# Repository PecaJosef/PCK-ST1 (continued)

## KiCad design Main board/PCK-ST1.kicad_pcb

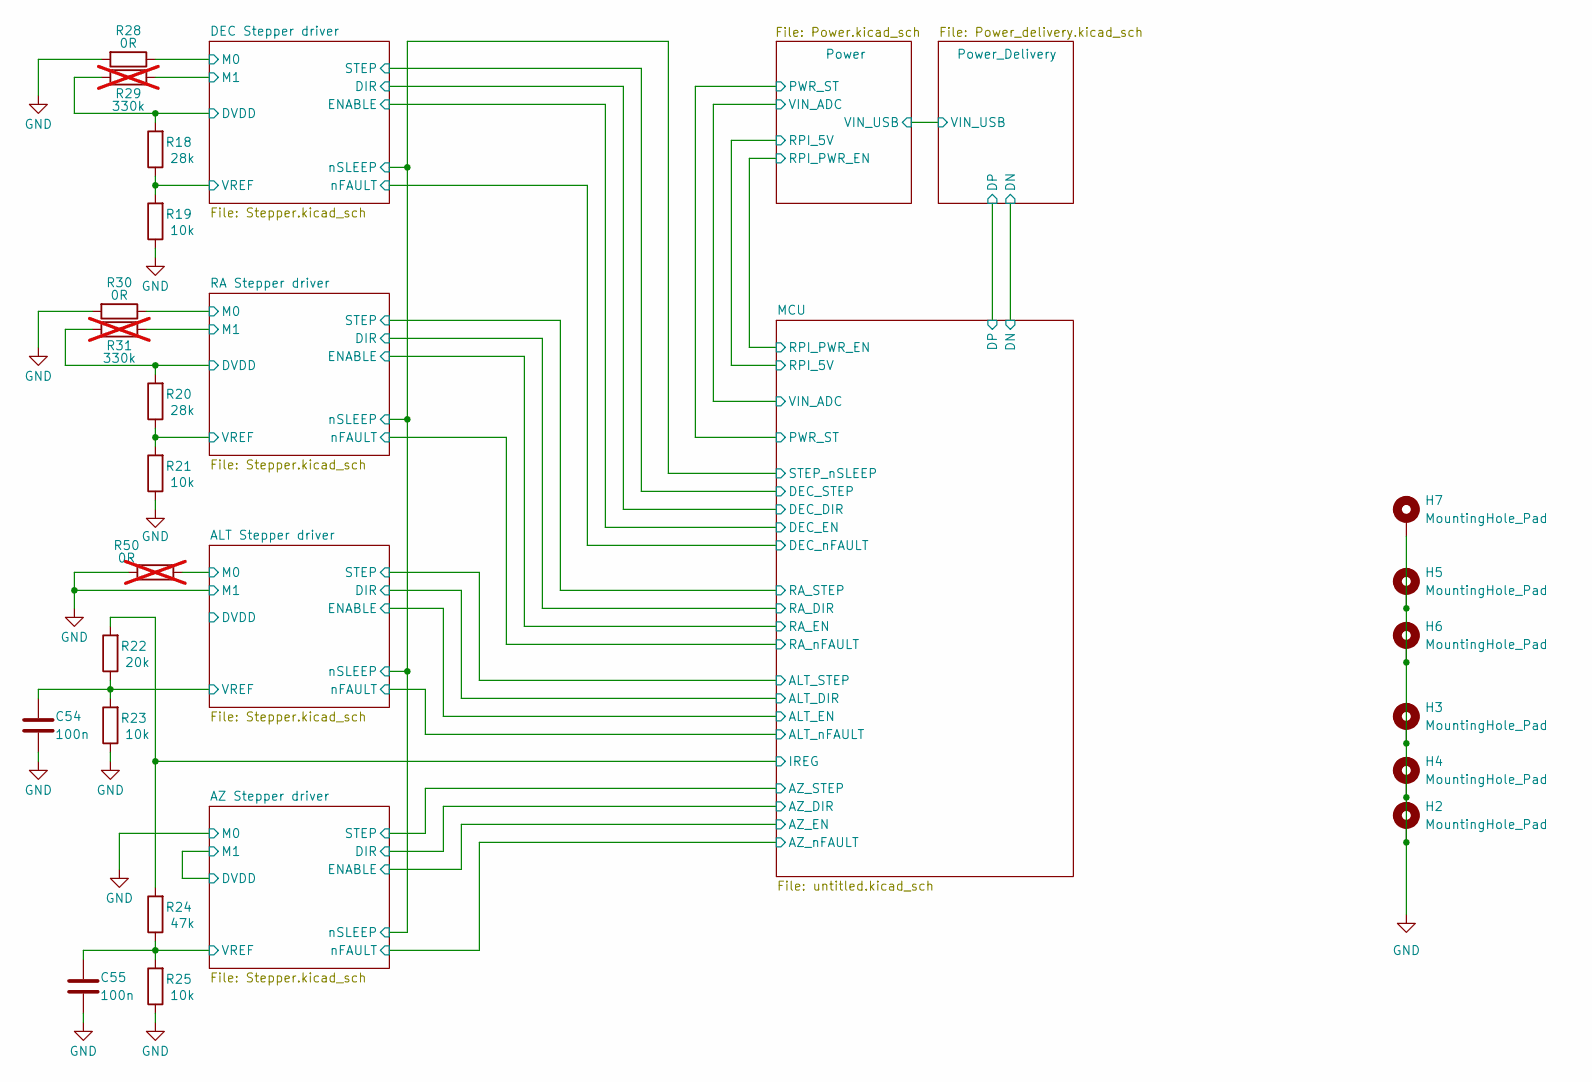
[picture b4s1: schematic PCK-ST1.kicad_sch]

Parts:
C54, C55: 100n; C_0402_1005Metric; Part Number GRM155R71C104JA88D
H2, H3, H4, H5, H6, H7: MountingHole_Pad; MountingHole_2.7mm_M2.5_DIN965_Pad
R18, R20: 28k; R_0402_1005Metric; Part Number CRCW040228K0FKED
R19, R21, R23, R25: 10k; R_0402_1005Metric; Part Number CRCW040210K0FKEDC
R22: 20k; R_0402_1005Metric; Part Number CRCW040220K0FKEDHP
R24: 47k; R_0402_1005Metric; Part Number CRCW040247K0FKED
R28, R30: 0R; R_0402_1005Metric; Part Number CRCW04020000Z0EDC
R29, R31: 330k; R_0402_1005Metric; Part Number CRCW0402330KFKED; not fitted
R50: 0R; R_0402_1005Metric; Part Number CRCW04020000Z0EDC; not fitted

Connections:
/ALT Stepper driver/M0: R50.2; also elsewhere on the board
/ALT Stepper driver/VREF: C54.1, R22.1, R23.2; also elsewhere on the board
/AZ Stepper driver/VREF: C55.1, R24.1, R25.2; also elsewhere on the board
/DEC Stepper driver/DVDD: R18.2, R29.1; also elsewhere on the board
/DEC Stepper driver/M0: R28.1; also elsewhere on the board
/DEC Stepper driver/M1: R29.2; also elsewhere on the board
/DEC Stepper driver/VREF: R18.1, R19.2; also elsewhere on the board
/MCU/IREG: R22.2, R24.2; also elsewhere on the board
/RA Stepper driver/DVDD: R20.2, R31.1; also elsewhere on the board
/RA Stepper driver/M0: R30.1; also elsewhere on the board
/RA Stepper driver/M1: R31.2; also elsewhere on the board
/RA Stepper driver/VREF: R20.1, R21.2; also elsewhere on the board
GND: C54.2, C55.2, H2.1, H3.1, H4.1, H5.1, H6.1, H7.1, R19.1, R21.1, R23.1, R25.1, R28.2, R30.2, R50.1; also elsewhere on the board

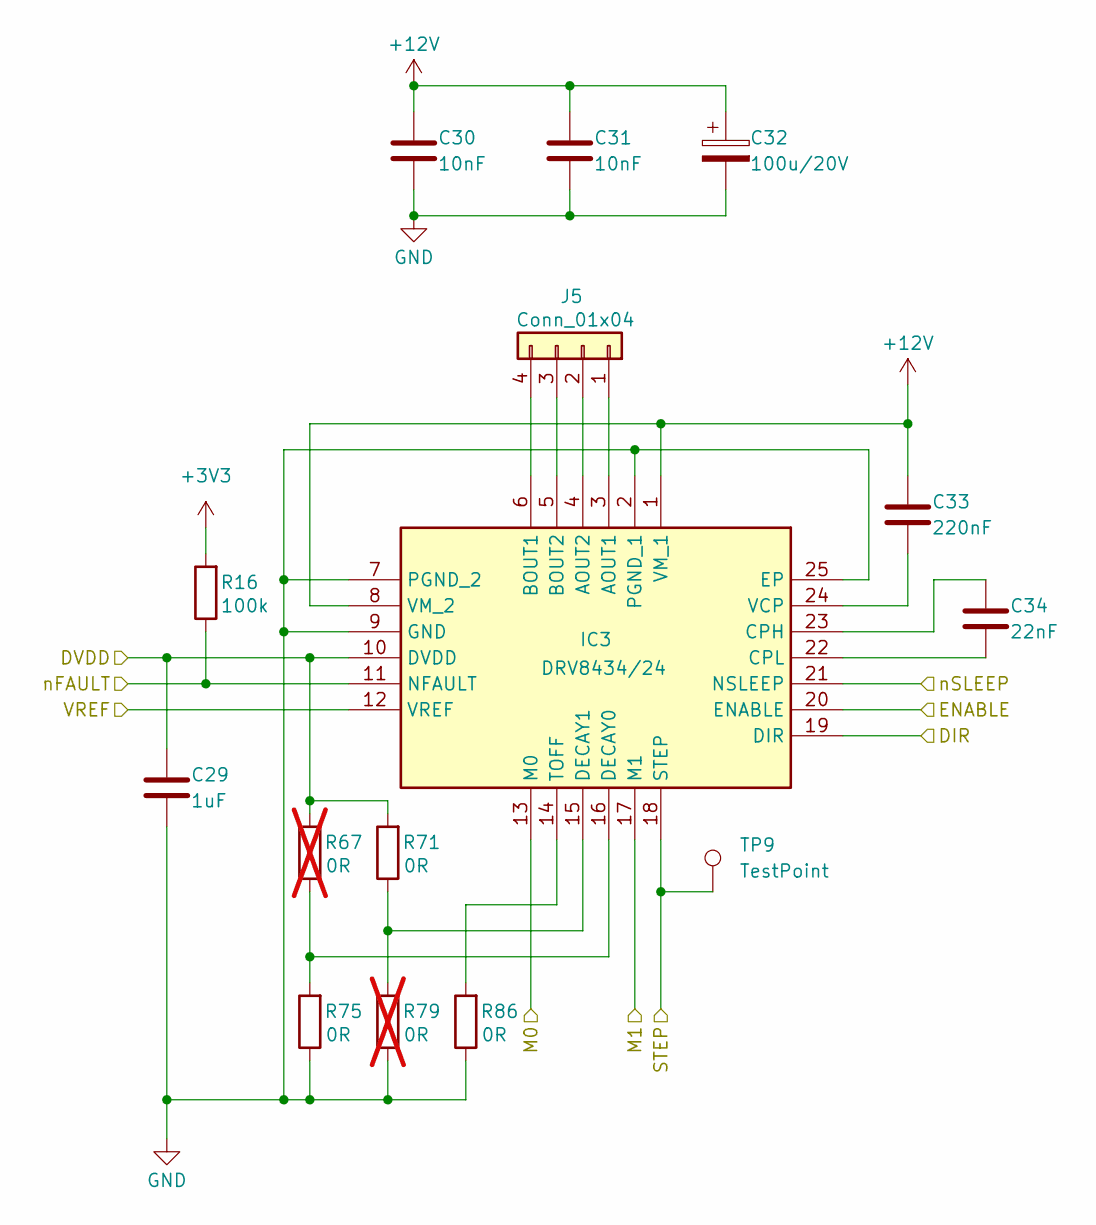
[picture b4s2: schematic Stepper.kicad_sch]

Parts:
C29: 1uF; C_0402_1005Metric; Part Number GRM155Z71A105KE01J
C30, C31: 10nF; C_0402_1005Metric; Part Number GRM155R71H103JA88D
C32: 100u/20V; CP_EIA-7343-15_Kemet-W; Part Number 293D107X9020D2TE3
C33: 220nF; C_0402_1005Metric; Part Number GCM155R71C224KE02J
C34: 22nF; C_0402_1005Metric; Part Number GRM155R71E223JA61D
IC3: DRV8434/24; QFN50P400X400X100-25N-D; Mouser Part Number DRV8434RGER
J5: Conn_01x04; JST_PH_B4B-PH-K_1x04_P2.00mm_Vertical
R16: 100k; R_0402_1005Metric; Part Number CRCW0402100KFKEE
R67, R79: 0R; R_0402_1005Metric; Part Number CRCW04020000Z0EDC; not fitted
R71, R75, R86: 0R; R_0402_1005Metric; Part Number CRCW04020000Z0EDC
TP9: TestPoint; TestPoint_Pad_D1.0mm

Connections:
+3V3: R16.2; also elsewhere on the board
+12V: C30.1, C31.1, C32.1, C33.1, IC3.1 (VM_1), IC3.8 (VM_2); also elsewhere on the board
/ALT Stepper driver/DIR: IC3.19 (DIR); also elsewhere on the board
/ALT Stepper driver/DVDD: C29.1, IC3.10 (DVDD), R67.2, R71.2
/ALT Stepper driver/ENABLE: IC3.20 (ENABLE); also elsewhere on the board
/ALT Stepper driver/M0: IC3.13 (M0); also elsewhere on the board
/ALT Stepper driver/STEP: IC3.18 (STEP), TP9.1; also elsewhere on the board
/ALT Stepper driver/VREF: IC3.12 (VREF); also elsewhere on the board
/ALT Stepper driver/nFAULT: IC3.11 (NFAULT), R16.1; also elsewhere on the board
/ALT Stepper driver/nSLEEP: IC3.21 (NSLEEP); also elsewhere on the board
GND: C29.2, C30.2, C31.2, C32.2, IC3.2 (PGND_1), IC3.7 (PGND_2), IC3.9 (GND), IC3.17 (M1), IC3.25 (EP), R75.1, R79.1, R86.1; also elsewhere on the board
unnamed: IC3.3 (AOUT1), J5.1
unnamed: IC3.4 (AOUT2), J5.2
unnamed: IC3.6 (BOUT1), J5.4
unnamed: IC3.5 (BOUT2), J5.3
unnamed: C34.1, IC3.23 (CPH)
unnamed: C34.2, IC3.22 (CPL)
unnamed: IC3.16 (DECAY0), R67.1, R75.2
unnamed: IC3.15 (DECAY1), R71.1, R79.2
unnamed: IC3.14 (TOFF), R86.2
unnamed: C33.2, IC3.24 (VCP)

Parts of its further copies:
C15, C28, C40: 22nF; C_0402_1005Metric; Part Number GRM155R71E223JA61D
C16, C23, C35: 1uF; C_0402_1005Metric; Part Number GRM155Z71A105KE01J
C17, C27, C39: 220nF; C_0402_1005Metric; Part Number GCM155R71C224KE02J
C18, C19, C24, C25, C36, C37: 10nF; C_0402_1005Metric; Part Number GRM155R71H103JA88D
C20, C26, C38: 100u/20V; CP_EIA-7343-15_Kemet-W; Part Number 293D107X9020D2TE3
IC1, IC2, IC4: DRV8434/24; QFN50P400X400X100-25N-D; Mouser Part Number DRV8434RGER
J3, J4, J6: Conn_01x04; JST_PH_B4B-PH-K_1x04_P2.00mm_Vertical
R14, R15, R17: 100k; R_0402_1005Metric; Part Number CRCW0402100KFKEE
R65, R66, R68, R77, R78, R80: 0R; R_0402_1005Metric; Part Number CRCW04020000Z0EDC; not fitted
R69, R70, R72, R73, R74, R76, R82, R84, R88: 0R; R_0402_1005Metric; Part Number CRCW04020000Z0EDC
TP7, TP8, TP10: TestPoint; TestPoint_Pad_D1.0mm

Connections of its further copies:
+3V3: R14.2, R15.2, R17.2; also elsewhere on the board
+12V: C17.1, C18.1, C19.1, C20.1, C24.1, C25.1, C26.1, C27.1, C36.1, C37.1, C38.1, C39.1, IC1.1 (VM_1), IC1.8 (VM_2), IC2.1 (VM_1), IC2.8 (VM_2), IC4.1 (VM_1), IC4.8 (VM_2); also elsewhere on the board
/ALT Stepper driver/nSLEEP: IC1.21 (NSLEEP), IC2.21 (NSLEEP), IC4.21 (NSLEEP); also elsewhere on the board
/AZ Stepper driver/DIR: IC4.19 (DIR); also elsewhere on the board
/AZ Stepper driver/DVDD: C35.1, IC4.10 (DVDD), IC4.17 (M1), R68.2, R72.2
/AZ Stepper driver/ENABLE: IC4.20 (ENABLE); also elsewhere on the board
/AZ Stepper driver/STEP: IC4.18 (STEP), TP10.1; also elsewhere on the board
/AZ Stepper driver/VREF: IC4.12 (VREF); also elsewhere on the board
/AZ Stepper driver/nFAULT: IC4.11 (NFAULT), R17.1; also elsewhere on the board
/DEC Stepper driver/DIR: IC1.19 (DIR); also elsewhere on the board
/DEC Stepper driver/DVDD: C16.1, IC1.10 (DVDD), R65.2, R69.2; also elsewhere on the board
/DEC Stepper driver/ENABLE: IC1.20 (ENABLE); also elsewhere on the board
/DEC Stepper driver/M0: IC1.13 (M0); also elsewhere on the board
/DEC Stepper driver/M1: IC1.17 (M1); also elsewhere on the board
/DEC Stepper driver/STEP: IC1.18 (STEP), TP7.1; also elsewhere on the board
/DEC Stepper driver/VREF: IC1.12 (VREF); also elsewhere on the board
/DEC Stepper driver/nFAULT: IC1.11 (NFAULT), R14.1; also elsewhere on the board
/MCU/RA_DIR: IC2.19 (DIR); also elsewhere on the board
/MCU/RA_EN: IC2.20 (ENABLE); also elsewhere on the board
/MCU/RA_STEP: IC2.18 (STEP), TP8.1; also elsewhere on the board
/MCU/RA_nFAULT: IC2.11 (NFAULT), R15.1; also elsewhere on the board
/RA Stepper driver/DVDD: C23.1, IC2.10 (DVDD), R66.2, R70.2; also elsewhere on the board
/RA Stepper driver/M0: IC2.13 (M0); also elsewhere on the board
/RA Stepper driver/M1: IC2.17 (M1); also elsewhere on the board
/RA Stepper driver/VREF: IC2.12 (VREF); also elsewhere on the board
GND: C16.2, C18.2, C19.2, C20.2, C23.2, C24.2, C25.2, C26.2, C35.2, C36.2, C37.2, C38.2, IC1.2 (PGND_1), IC1.7 (PGND_2), IC1.9 (GND), IC1.25 (EP), IC2.2 (PGND_1), IC2.7 (PGND_2), IC2.9 (GND), IC2.25 (EP), IC4.2 (PGND_1), IC4.7 (PGND_2), IC4.9 (GND), IC4.13 (M0), IC4.25 (EP), R73.1, R74.1, R76.1, R77.1, R78.1, R80.1, R82.1, R84.1, R88.1; also elsewhere on the board
unnamed: IC1.3 (AOUT1), J3.1
unnamed: IC1.4 (AOUT2), J3.2
unnamed: IC1.6 (BOUT1), J3.4
unnamed: IC1.5 (BOUT2), J3.3
unnamed: C15.1, IC1.23 (CPH)
unnamed: C15.2, IC1.22 (CPL)
unnamed: IC1.16 (DECAY0), R65.1, R73.2
unnamed: IC1.15 (DECAY1), R69.1, R77.2
unnamed: IC1.14 (TOFF), R82.2
unnamed: C17.2, IC1.24 (VCP)
unnamed: IC2.3 (AOUT1), J4.1
unnamed: IC2.4 (AOUT2), J4.2
unnamed: IC2.6 (BOUT1), J4.4
unnamed: IC2.5 (BOUT2), J4.3
unnamed: C28.1, IC2.23 (CPH)
unnamed: C28.2, IC2.22 (CPL)
unnamed: IC2.16 (DECAY0), R66.1, R74.2
unnamed: IC2.15 (DECAY1), R70.1, R78.2
unnamed: IC2.14 (TOFF), R84.2
unnamed: C27.2, IC2.24 (VCP)
unnamed: IC4.3 (AOUT1), J6.1
unnamed: IC4.4 (AOUT2), J6.2
unnamed: IC4.6 (BOUT1), J6.4
unnamed: IC4.5 (BOUT2), J6.3
unnamed: C40.1, IC4.23 (CPH)
unnamed: C40.2, IC4.22 (CPL)
unnamed: IC4.16 (DECAY0), R68.1, R76.2
unnamed: IC4.15 (DECAY1), R72.1, R80.2
unnamed: IC4.14 (TOFF), R88.2
unnamed: C39.2, IC4.24 (VCP)

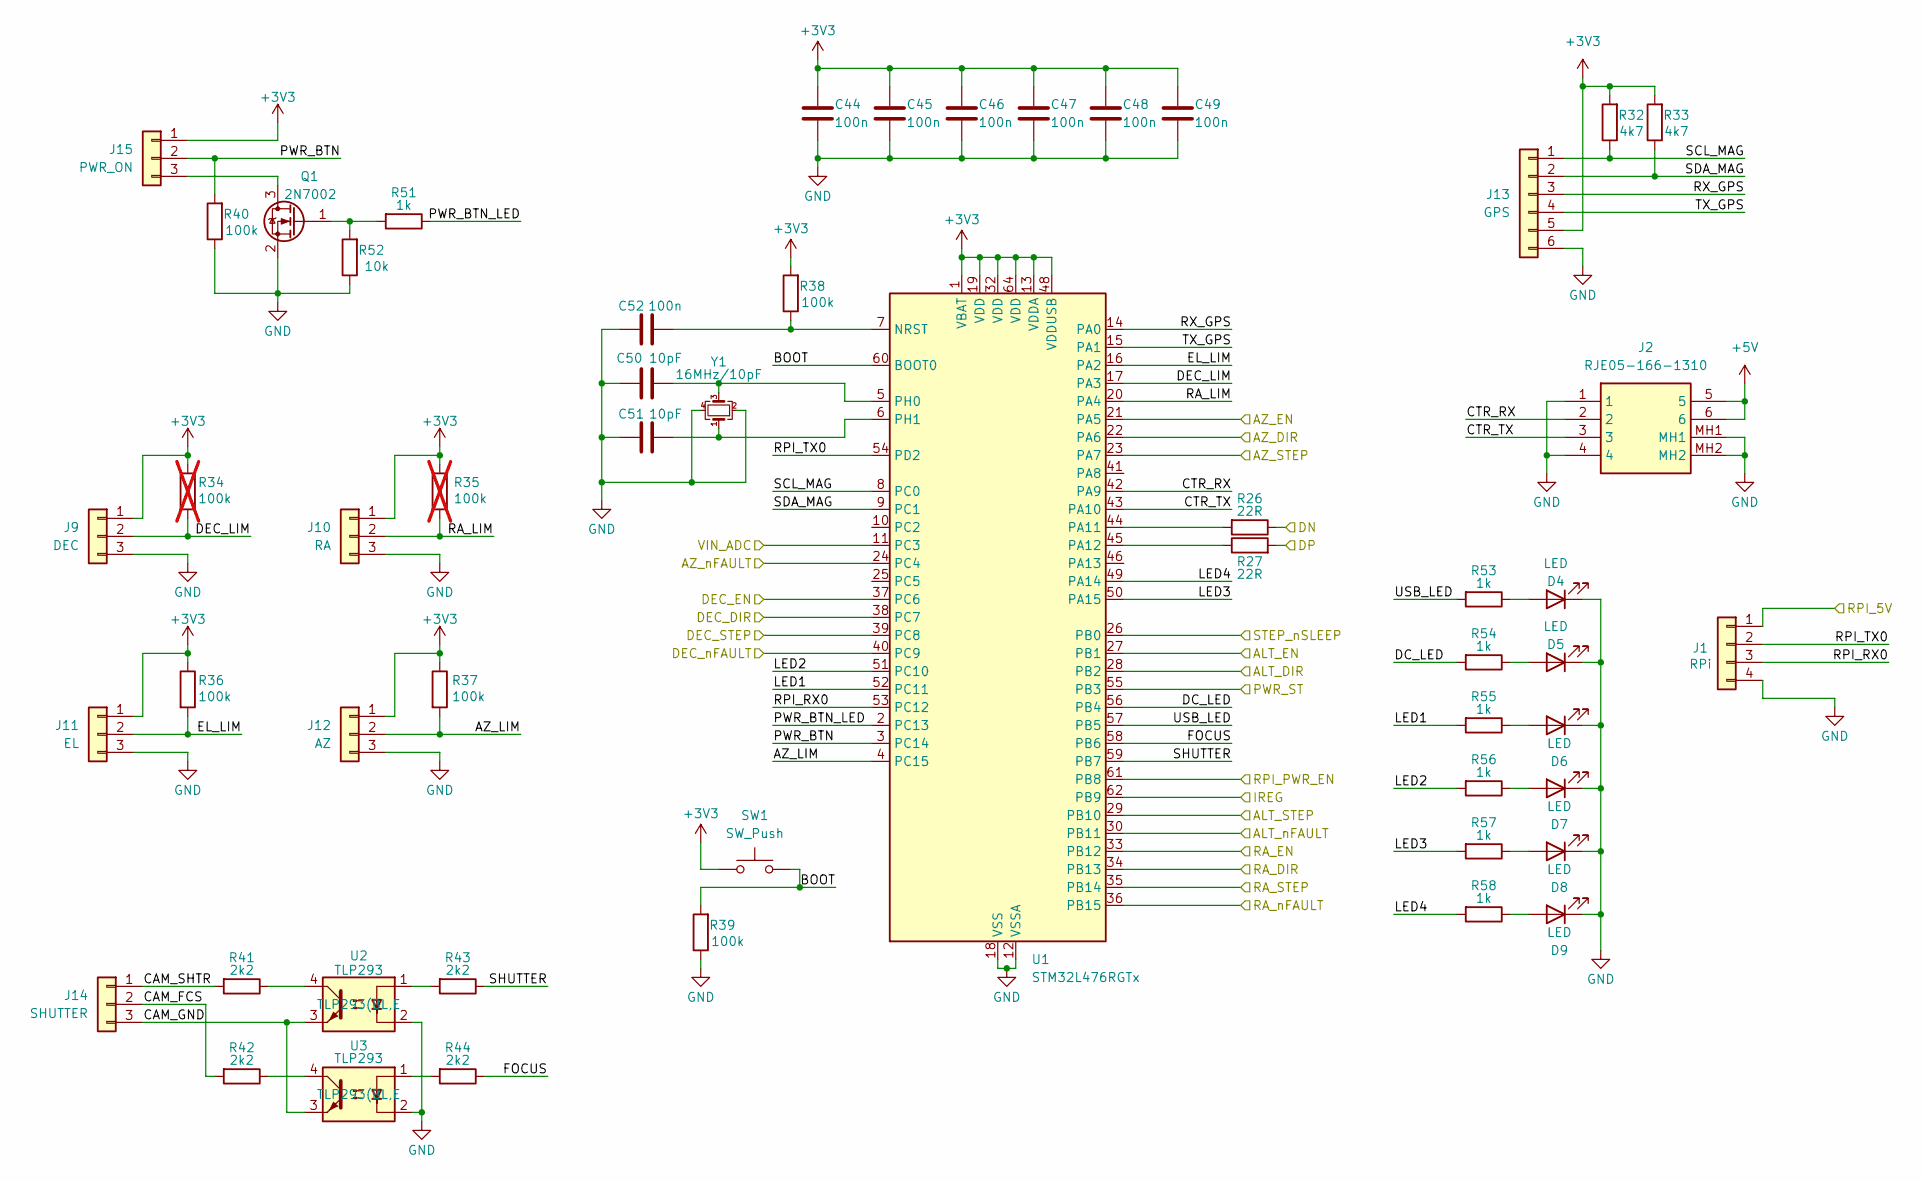
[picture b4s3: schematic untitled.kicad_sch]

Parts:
C44, C45, C46, C47, C48, C49, C52: 100n; C_0402_1005Metric; Part Number GRM155R71C104JA88D
C50, C51: 10pF; C_0402_1005Metric; Part Number GCM1555C1H100FA16D
D4, D5, D6, D7, D8, D9: LED; LED_0603_1608Metric; Part Number SML-D12U1WT86
J1: RPi; JST_PH_B4B-PH-K_1x04_P2.00mm_Vertical
J2: RJE05-166-1310; RJE051661310; Mouser Part Number 523-RJE05-166-1310
J9: DEC; JST_PH_B3B-PH-K_1x03_P2.00mm_Vertical
J10: RA; JST_PH_B3B-PH-K_1x03_P2.00mm_Vertical
J11: EL; JST_PH_B3B-PH-K_1x03_P2.00mm_Vertical
J12: AZ; JST_PH_B3B-PH-K_1x03_P2.00mm_Vertical
J13: GPS; JST_PH_B6B-PH-K_1x06_P2.00mm_Vertical
J14: SHUTTER; JST_PH_B3B-PH-K_1x03_P2.00mm_Vertical
J15: PWR_ON; JST_PH_B3B-PH-K_1x03_P2.00mm_Vertical
Q1: 2N7002; SOT-323_SC-70; Part Number 2N7002AKW-QX
R26, R27: 22R; R_0402_1005Metric; Part Number CRCW040222R0FKED
R32, R33: 4k7; R_0402_1005Metric; Part Number CRCW04024K70FKED
R34, R35: 100k; R_0402_1005Metric; Part Number CRCW0402100KFKEE; not fitted
R36, R37, R38, R39, R40: 100k; R_0402_1005Metric; Part Number CRCW0402100KFKEE
R41, R42, R43, R44: 2k2; R_0402_1005Metric; Part Number CRCW04022K20FKEDC
R51, R53, R54, R55, R56, R57, R58: 1k; R_0402_1005Metric; Part Number CRCW04021K00FKED
R52: 10k; R_0402_1005Metric; Part Number CRCW040210K0FKEDC
SW1: SW_Push; SKRTLAE010
U1: STM32L476RGTx; LQFP-64_10x10mm_P0.5mm; Part Number STM32L476RGT6
U2, U3: TLP293; SOIC-4_4.55x2.6mm_P1.27mm; Part Number TLP293(BL,E
Y1: 16MHz/10pF; Crystal_SMD_2016-4Pin_2.0x1.6mm; Part Number ECS1601037B2CTNTR

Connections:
+3V3: C44.1, C45.1, C46.1, C47.1, C48.1, C49.1, J9.1, J10.1, J11.1, J12.1, J13.5, J15.1, R32.2, R33.2, R34.1, R35.1, R36.1, R37.1, R38.2, SW1.1, U1.1 (VBAT), U1.13 (VDDA), U1.19 (VDD), U1.32 (VDD), U1.48 (VDDUSB), U1.64 (VDD); also elsewhere on the board
+5V: J2.5, J2.6; also elsewhere on the board
/ALT Stepper driver/DIR: U1.28 (PB2); also elsewhere on the board
/ALT Stepper driver/ENABLE: U1.27 (PB1); also elsewhere on the board
/ALT Stepper driver/STEP: U1.29 (PB10); also elsewhere on the board
/ALT Stepper driver/nFAULT: U1.30 (PB11); also elsewhere on the board
/ALT Stepper driver/nSLEEP: U1.26 (PB0); also elsewhere on the board
/AZ Stepper driver/DIR: U1.22 (PA6); also elsewhere on the board
/AZ Stepper driver/ENABLE: U1.21 (PA5); also elsewhere on the board
/AZ Stepper driver/STEP: U1.23 (PA7); also elsewhere on the board
/AZ Stepper driver/nFAULT: U1.24 (PC4); also elsewhere on the board
/DEC Stepper driver/DIR: U1.38 (PC7); also elsewhere on the board
/DEC Stepper driver/ENABLE: U1.37 (PC6); also elsewhere on the board
/DEC Stepper driver/STEP: U1.39 (PC8); also elsewhere on the board
/DEC Stepper driver/nFAULT: U1.40 (PC9); also elsewhere on the board
/MCU/AZ_LIM: J12.2, R37.2, U1.4 (PC15)
/MCU/BOOT: R39.2, SW1.2, U1.60 (BOOT0)
/MCU/CAM_FCS: J14.2, R42.2
/MCU/CAM_GND: J14.3, U2.3, U3.3
/MCU/CAM_SHTR: J14.1, R41.2
/MCU/CTR_RX: J2.2, U1.42 (PA9)
/MCU/CTR_TX: J2.3, U1.43 (PA10)
/MCU/DC_LED: R54.2, U1.56 (PB4)
/MCU/DEC_LIM: J9.2, R34.2, U1.17 (PA3)
/MCU/DN: R26.1; also elsewhere on the board
/MCU/DP: R27.2; also elsewhere on the board
/MCU/EL_LIM: J11.2, R36.2, U1.16 (PA2)
/MCU/FOCUS: R44.1, U1.58 (PB6)
/MCU/IREG: U1.62 (PB9); also elsewhere on the board
/MCU/LED1: R55.2, U1.52 (PC11)
/MCU/LED2: R56.2, U1.51 (PC10)
/MCU/LED3: R57.2, U1.50 (PA15)
/MCU/LED4: R58.2, U1.49 (PA14)
/MCU/PWR_BTN: J15.2, R40.2, U1.3 (PC14)
/MCU/PWR_BTN_LED: R51.1, U1.2 (PC13)
/MCU/RA_DIR: U1.34 (PB13); also elsewhere on the board
/MCU/RA_EN: U1.33 (PB12); also elsewhere on the board
/MCU/RA_LIM: J10.2, R35.2, U1.20 (PA4)
/MCU/RA_STEP: U1.35 (PB14); also elsewhere on the board
/MCU/RA_nFAULT: U1.36 (PB15); also elsewhere on the board
/MCU/RPI_5V: J1.1; also elsewhere on the board
/MCU/RPI_PWR_EN: U1.61 (PB8); also elsewhere on the board
/MCU/RPI_RX0: J1.3, U1.53 (PC12)
/MCU/RPI_TX0: J1.2, U1.54 (PD2)
/MCU/RX_GPS: J13.3, U1.14 (PA0)
/MCU/SCL_MAG: J13.1, R32.1, U1.8 (PC0)
/MCU/SDA_MAG: J13.2, R33.1, U1.9 (PC1)
/MCU/SHUTTER: R43.1, U1.59 (PB7)
/MCU/TX_GPS: J13.4, U1.15 (PA1)
/MCU/USB_LED: R53.2, U1.57 (PB5)
/MCU/VIN_ADC: U1.11 (PC3); also elsewhere on the board
/Power/PWR_STATE: U1.55 (PB3); also elsewhere on the board
GND: C44.2, C45.2, C46.2, C47.2, C48.2, C49.2, C50.1, C51.1, C52.1, D4.1 (K), D5.1 (K), D6.1 (K), D7.1 (K), D8.1 (K), D9.1 (K), J1.4, J2.1, J2.4, J2.MH1, J2.MH2, J9.3, J10.3, J11.3, J12.3, J13.6, Q1.2 (S), R39.1, R40.1, R52.1, U1.12 (VSSA), U1.18 (VSS), U1.31 (VSS), U1.47 (VSS), U1.63 (VSS), U2.2, U3.2, Y1.2, Y1.4; also elsewhere on the board
unnamed: D4.2 (A), R53.1
unnamed: D5.2 (A), R54.1
unnamed: D6.2 (A), R55.1
unnamed: D7.2 (A), R56.1
unnamed: D8.2 (A), R57.1
unnamed: D9.2 (A), R58.1
unnamed: J15.3, Q1.3 (D)
unnamed: Q1.1 (G), R51.2, R52.2
unnamed: R41.1, U2.4
unnamed: R42.1, U3.4
unnamed: R43.2, U2.1
unnamed: R44.2, U3.1
unnamed: C52.2, R38.1, U1.7 (NRST)
unnamed: R26.2, U1.44 (PA11)
unnamed: R27.1, U1.45 (PA12)
unnamed: C50.2, U1.5 (PH0), Y1.3
unnamed: C51.2, U1.6 (PH1), Y1.1

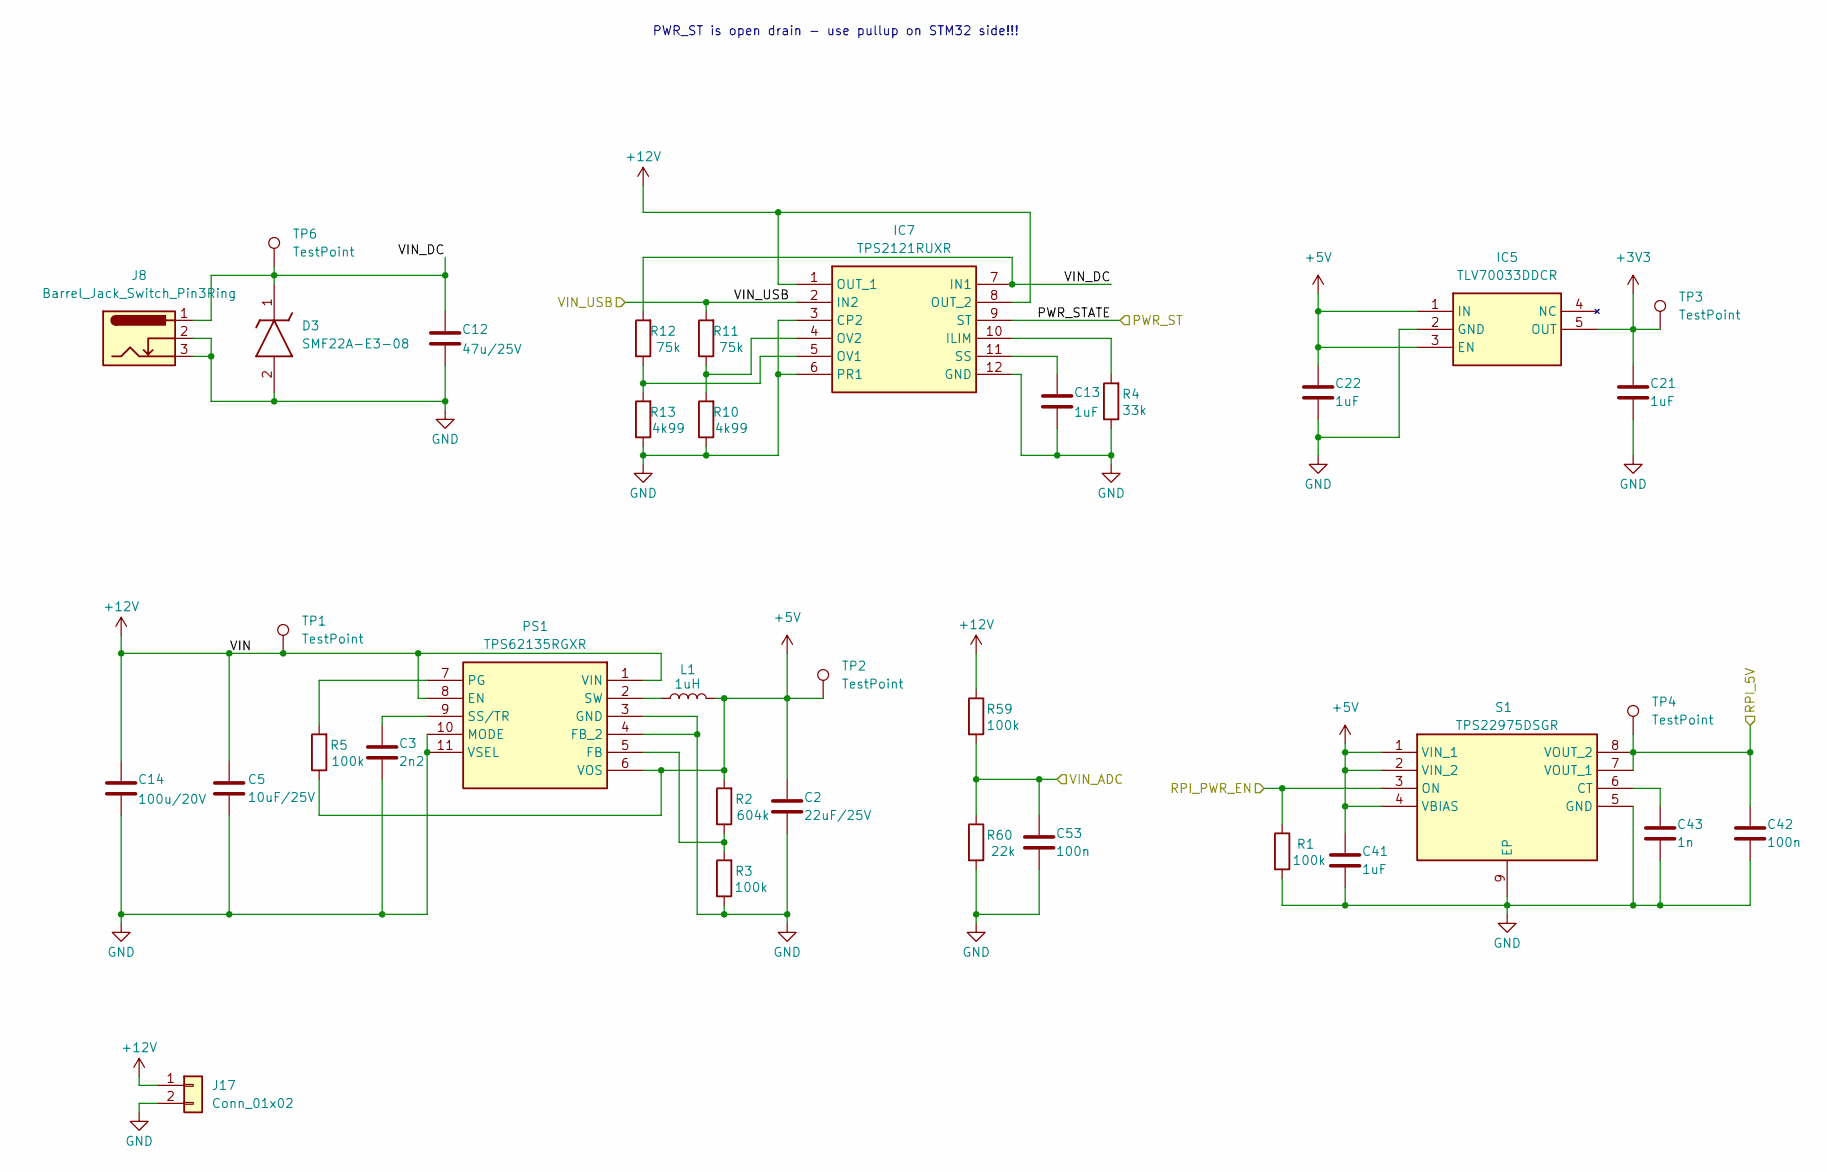
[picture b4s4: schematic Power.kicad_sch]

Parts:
C2: 22uF/25V; C_0805_2012Metric; Part Number CL21A226MAYNNNE
C3: 2n2; C_0402_1005Metric; Part Number GRM155R71H222JA01J
C5: 10uF/25V; C_0603_1608Metric; Part Number GRM188R61E106KA73J
C12: 47u/25V; C_1206_3216Metric; Part Number C3216X5R1E476M160AC
C13, C21, C22, C41: 1uF; C_0402_1005Metric; Part Number GRM155Z71A105KE01J
C14: 100u/20V; CP_EIA-7343-15_Kemet-W; Part Number 293D107X9020D2TE3
C42, C53: 100n; C_0402_1005Metric; Part Number GRM155R71C104JA88D
C43: 1n; C_0402_1005Metric; Part Number GRT1555C1H102FA02D
D3: SMF22A-E3-08; SODFL3718X108N; Mouser Part Number 78-SMF22A-E3-08
IC5: TLV70033DDCR; SOT95P280X110-5N; Mouser Part Number 595-TLV70033DDCR
IC7: TPS2121RUXR; Mouser Part Number 595-TPS2121RUXR
J8: Barrel_Jack_Switch_Pin3Ring; BarrelJack_GCT_DCJ200-10-A_Horizontal
J17: Conn_01x02; JST_PH_B2B-PH-K_1x02_P2.00mm_Vertical
L1: 1uH; L_Coilcraft_XAL4020-XXX; Part Number 74439323010
PS1: TPS62135RGXR; TPS621361RGXT; Mouser Part Number 595-TPS62135RGXR
R1: 100k; R_0402_1005Metric; Part Number CRCW040222K0FKEDHP
R2: 604k; R_0402_1005Metric; Part Number CRCW0402604KFKEDC
R3, R5, R59: 100k; R_0402_1005Metric; Part Number CRCW0402100KFKEE
R4: 33k; R_0402_1005Metric; Part Number CRCW040233K0FKEDHP
R10, R13: 4k99; R_0402_1005Metric; Part Number CRCW04024K99FKED
R11, R12: 75k; R_0402_1005Metric; Part Number CRCW040275K0FKED
R60: 22k; R_0402_1005Metric; Part Number CRCW040222K0FKEDHP
S1: TPS22975DSGR; SON50P200X200X80-9N; Mouser Part Number 595-TPS22975DSGR
TP1, TP2, TP3, TP4, TP6: TestPoint; TestPoint_Pad_D1.0mm

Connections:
+3V3: C21.1, IC5.5 (OUT), TP3.1; also elsewhere on the board
+5V: C2.1, C22.1, C41.1, IC5.1 (IN), IC5.3 (EN), L1.2, PS1.6 (VOS), R2.2, R5.1, S1.1 (VIN_1), S1.2 (VIN_2), S1.4 (VBIAS), TP2.1; also elsewhere on the board
+12V: C5.1, C14.1, IC7.1 (OUT_1), IC7.8 (OUT_2), J17.1, PS1.1 (VIN), PS1.8 (EN), R59.1, TP1.1; also elsewhere on the board
/MCU/RPI_5V: C42.1, S1.7 (VOUT_1), S1.8 (VOUT_2), TP4.1; also elsewhere on the board
/MCU/RPI_PWR_EN: R1.1, S1.3 (ON); also elsewhere on the board
/MCU/VIN_ADC: C53.1, R59.2, R60.1; also elsewhere on the board
/Power/PWR_STATE: IC7.9 (ST); also elsewhere on the board
/Power/VIN_DC: C12.1, D3.1 (K), IC7.7 (IN1), J8.1, R12.2, TP6.1
/Power/VIN_USB: IC7.2 (IN2), R11.2; also elsewhere on the board
GND: C2.2, C3.2, C5.2, C12.2, C13.2, C14.2, C21.2, C22.2, C41.2, C42.2, C43.2, C53.2, D3.2 (A), IC5.2 (GND), IC7.3 (CP2), IC7.6 (PR1), IC7.12 (GND), J8.2, J8.3, J17.2, PS1.3 (GND), PS1.4 (FB_2), PS1.10 (MODE), PS1.11 (VSEL), R1.2, R3.1, R4.1, R10.1, R13.1, R60.2, S1.5 (GND), S1.9 (EP); also elsewhere on the board
unnamed: IC7.10 (ILIM), R4.2
unnamed: IC7.5 (OV1), R12.1, R13.2
unnamed: IC7.4 (OV2), R10.2, R11.1
unnamed: C13.1, IC7.11 (SS)
unnamed: PS1.5 (FB), R2.1, R3.2
unnamed: PS1.7 (PG), R5.2
unnamed: C3.1, PS1.9 (SS/TR)
unnamed: L1.1, PS1.2 (SW)
unnamed: C43.1, S1.6 (CT)

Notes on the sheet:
PWR_ST is open drain - use pullup on STM32 side!!!

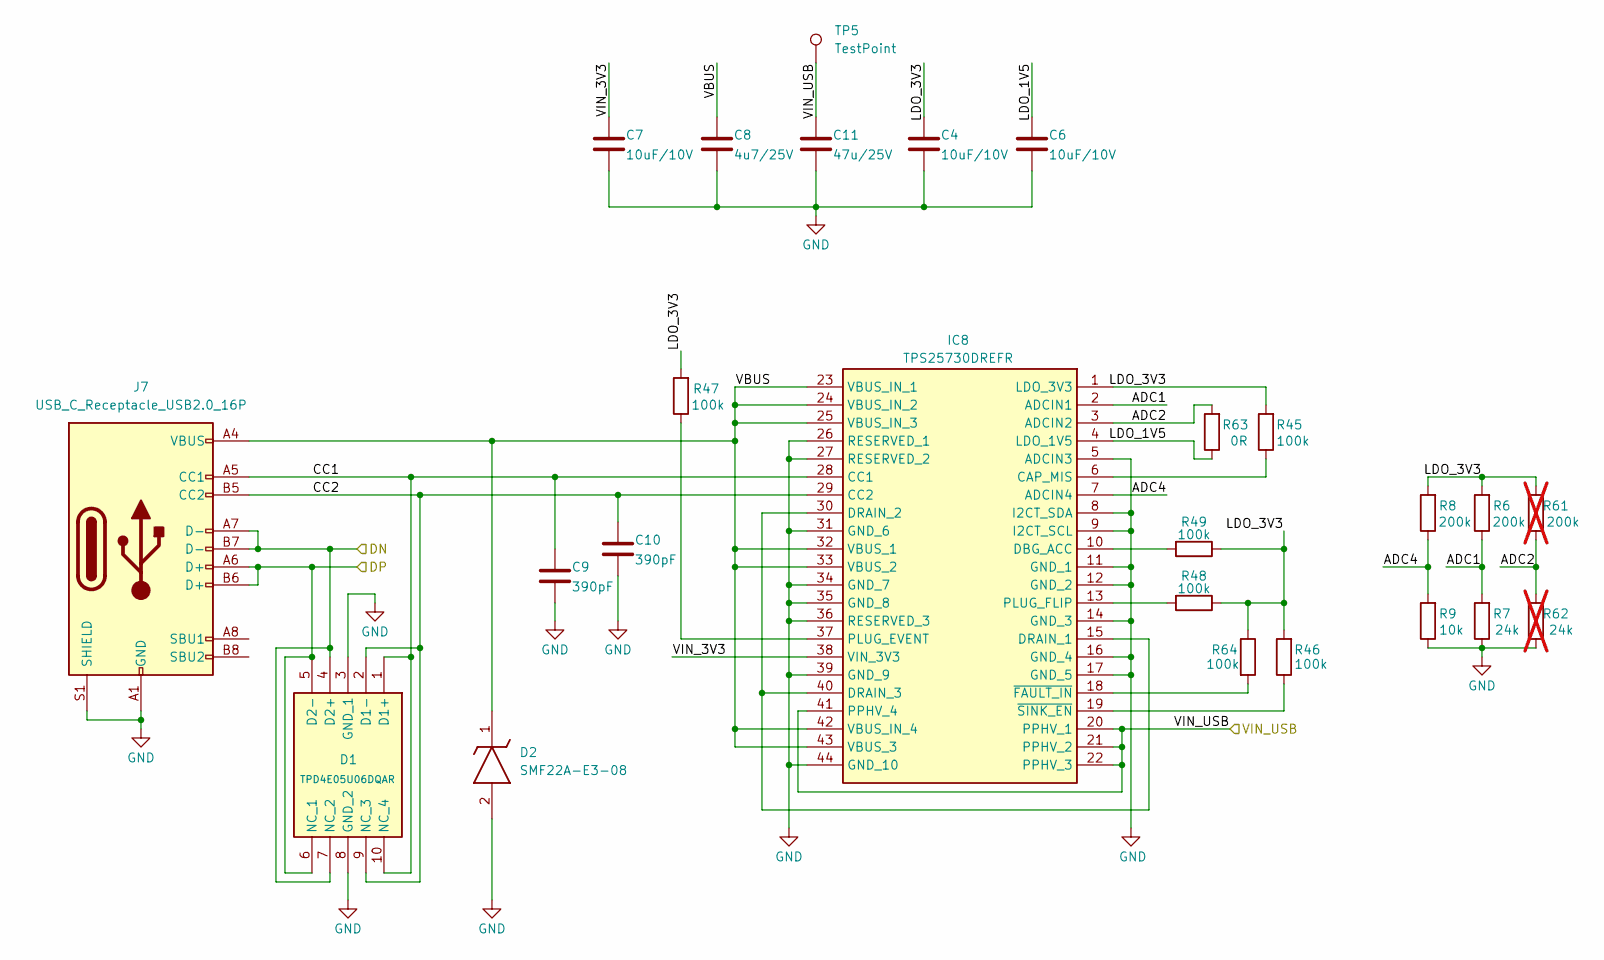
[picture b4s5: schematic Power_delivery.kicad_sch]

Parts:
C4, C6, C7: 10uF/10V; C_0402_1005Metric; Part Number GRM155R61A106ME11D
C8: 4u7/25V; C_0603_1608Metric; Part Number GRM188R61E475KE11D
C9, C10: 390pF; C_0402_1005Metric; Part Number GRM1555C2A391JE01D
C11: 47u/25V; C_1206_3216Metric; Part Number C3216X5R1E476M160AC
D1: TPD4E05U06DQAR; DQA_R-PUSON-N10_; Mouser Part Number 595-TPD4E05U06DQAR
D2: SMF22A-E3-08; SODFL3718X108N; Mouser Part Number 78-SMF22A-E3-08
IC8: TPS25730DREFR; Mouser Part Number 595-TPS25730DREFR
J7: USB_C_Receptacle_USB2.0_16P; USB_C_Receptacle_HCTL_HC-TYPE-C-16P-01A
R6, R8: 200k; R_0402_1005Metric; Part Number CRCW0402200KFKEDHP
R7: 24k; R_0402_1005Metric; Part Number CRCW040224K0FKEDC
R9: 10k; R_0402_1005Metric; Part Number CRCW040210K0FKEDC
R45, R46, R47, R48, R49, R64: 100k; R_0402_1005Metric; Part Number CRCW0402100KFKEE
R61: 200k; R_0402_1005Metric; Part Number CRCW0402200KFKEDHP; not fitted
R62: 24k; R_0402_1005Metric; Part Number CRCW040224K0FKEDC; not fitted
R63: 0R; R_0402_1005Metric; Part Number CRCW04020000Z0EDC
TP5: TestPoint; TestPoint_Pad_D1.0mm

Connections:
/MCU/DN: D1.4 (D2+), D1.7 (NC_2), J7.A7 (D-), J7.B7 (D-); also elsewhere on the board
/MCU/DP: D1.5 (D2-), D1.6 (NC_1), J7.A6 (D+), J7.B6 (D+); also elsewhere on the board
/Power/VIN_USB: C11.1, IC8.20 (PPHV_1), IC8.21 (PPHV_2), IC8.22 (PPHV_3), IC8.41 (PPHV_4), TP5.1; also elsewhere on the board
/Power_Delivery/ADC1: IC8.2 (ADCIN1), R6.1, R7.2
/Power_Delivery/ADC2: IC8.3 (ADCIN2), R61.1, R62.2, R63.2
/Power_Delivery/ADC4: IC8.7 (ADCIN4), R8.1, R9.2
/Power_Delivery/CC1: C9.1, D1.1 (D1+), D1.10 (NC_4), IC8.28 (CC1), J7.A5 (CC1)
/Power_Delivery/CC2: C10.1, D1.2 (D1-), D1.9 (NC_3), IC8.29 (CC2), J7.B5 (CC2)
/Power_Delivery/LDO_1V5: C6.1, IC8.4 (LDO_1V5), R63.1
/Power_Delivery/LDO_3V3: C4.1, IC8.1 (LDO_3V3), R6.2, R8.2, R45.2, R46.2, R47.2, R48.1, R49.1, R61.2, R64.1
/Power_Delivery/VBUS: C8.1, D2.1 (K), IC8.23 (VBUS_IN_1), IC8.24 (VBUS_IN_2), IC8.25 (VBUS_IN_3), IC8.32 (VBUS_1), IC8.33 (VBUS_2), IC8.42 (VBUS_IN_4), IC8.43 (VBUS_3), J7.A4 (VBUS), J7.A9 (VBUS), J7.B4 (VBUS), J7.B9 (VBUS)
/Power_Delivery/VIN_3V3: C7.1, IC8.38 (VIN_3V3)
GND: C4.2, C6.2, C7.2, C8.2, C9.2, C10.2, C11.2, D1.3 (GND_1), D1.8 (GND_2), D2.2 (A), IC8.5 (ADCIN3), IC8.8 (I2CT_SDA), IC8.9 (I2CT_SCL), IC8.11 (GND_1), IC8.12 (GND_2), IC8.14 (GND_3), IC8.16 (GND_4), IC8.17 (GND_5), IC8.26 (RESERVED_1), IC8.27 (RESERVED_2), IC8.31 (GND_6), IC8.34 (GND_7), IC8.35 (GND_8), IC8.36 (RESERVED_3), IC8.39 (GND_9), IC8.44 (GND_10), J7.A1 (GND), J7.A12 (GND), J7.B1 (GND), J7.B12 (GND), J7.S1 (SHIELD), R7.1, R9.1, R62.1; also elsewhere on the board
unnamed: IC8.6 (CAP_MIS), R45.1
unnamed: IC8.10 (DBG_ACC), R49.2
unnamed: IC8.15 (DRAIN_1), IC8.30 (DRAIN_2), IC8.40 (DRAIN_3)
unnamed: IC8.37 (PLUG_EVENT), R47.1
unnamed: IC8.13 (PLUG_FLIP), R48.2
unnamed: IC8.18 (~FAULT_IN), R64.2
unnamed: IC8.19 (~SINK_EN), R46.1

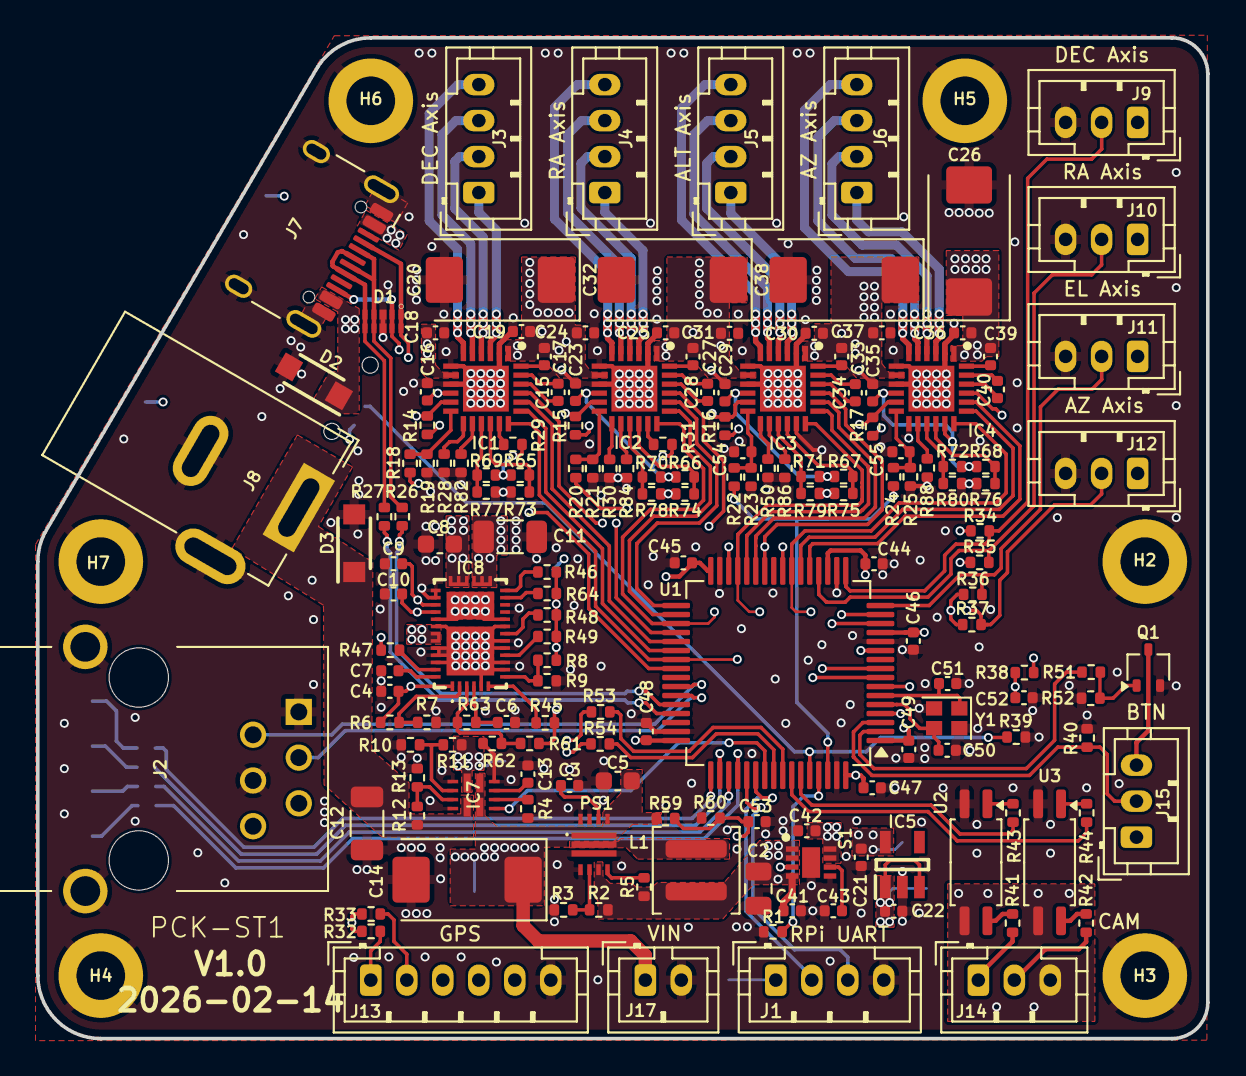
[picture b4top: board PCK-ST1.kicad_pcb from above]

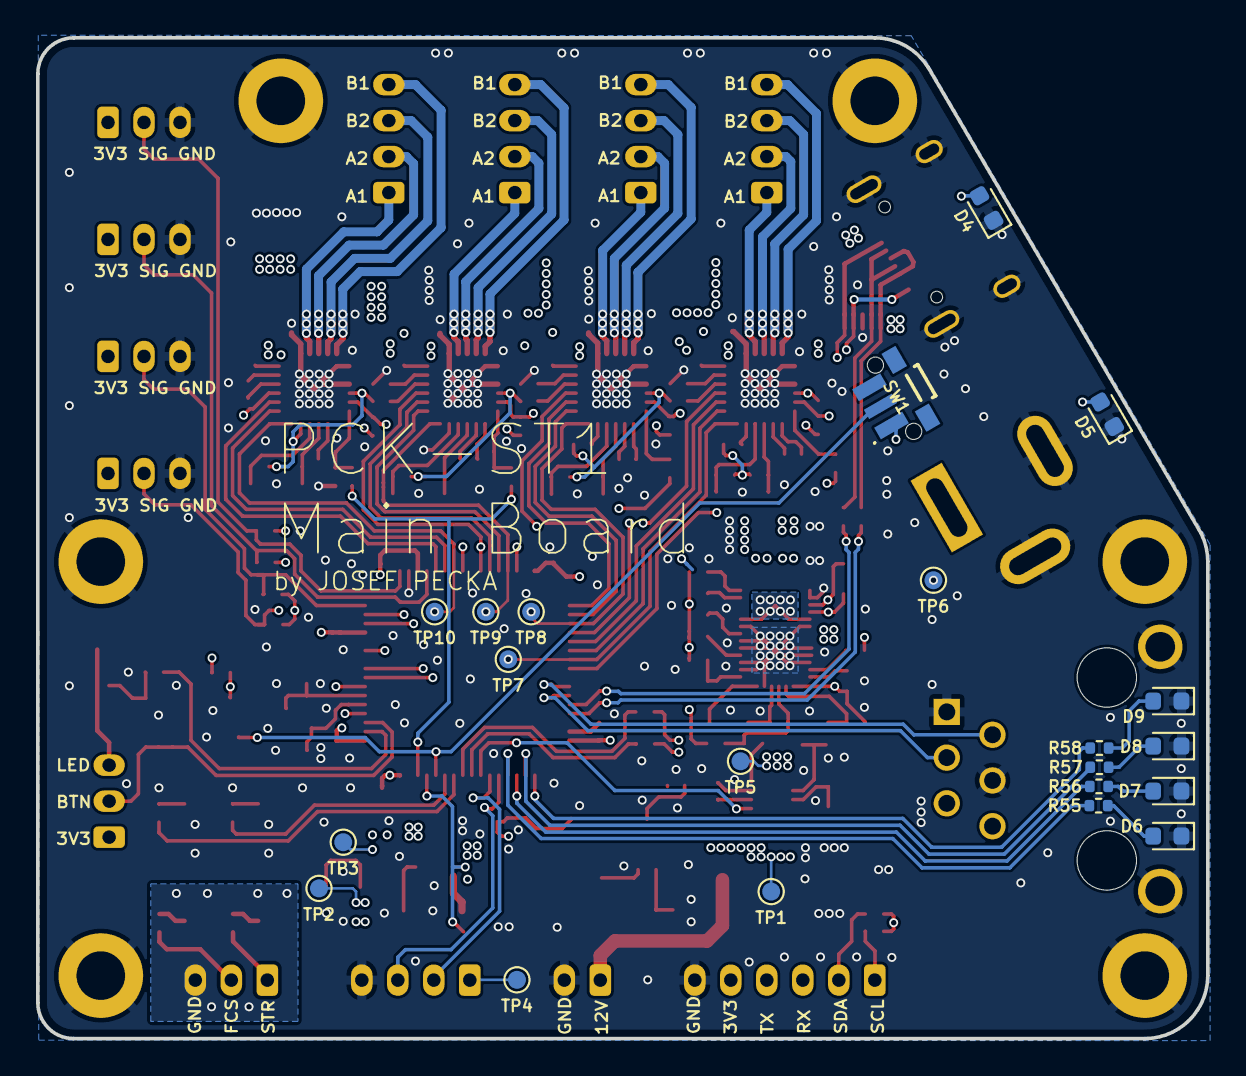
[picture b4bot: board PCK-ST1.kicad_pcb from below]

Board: 4 copper layers, 65.0 x 55.6 mm, 195 parts (21 on the bottom side), 151 nets.
